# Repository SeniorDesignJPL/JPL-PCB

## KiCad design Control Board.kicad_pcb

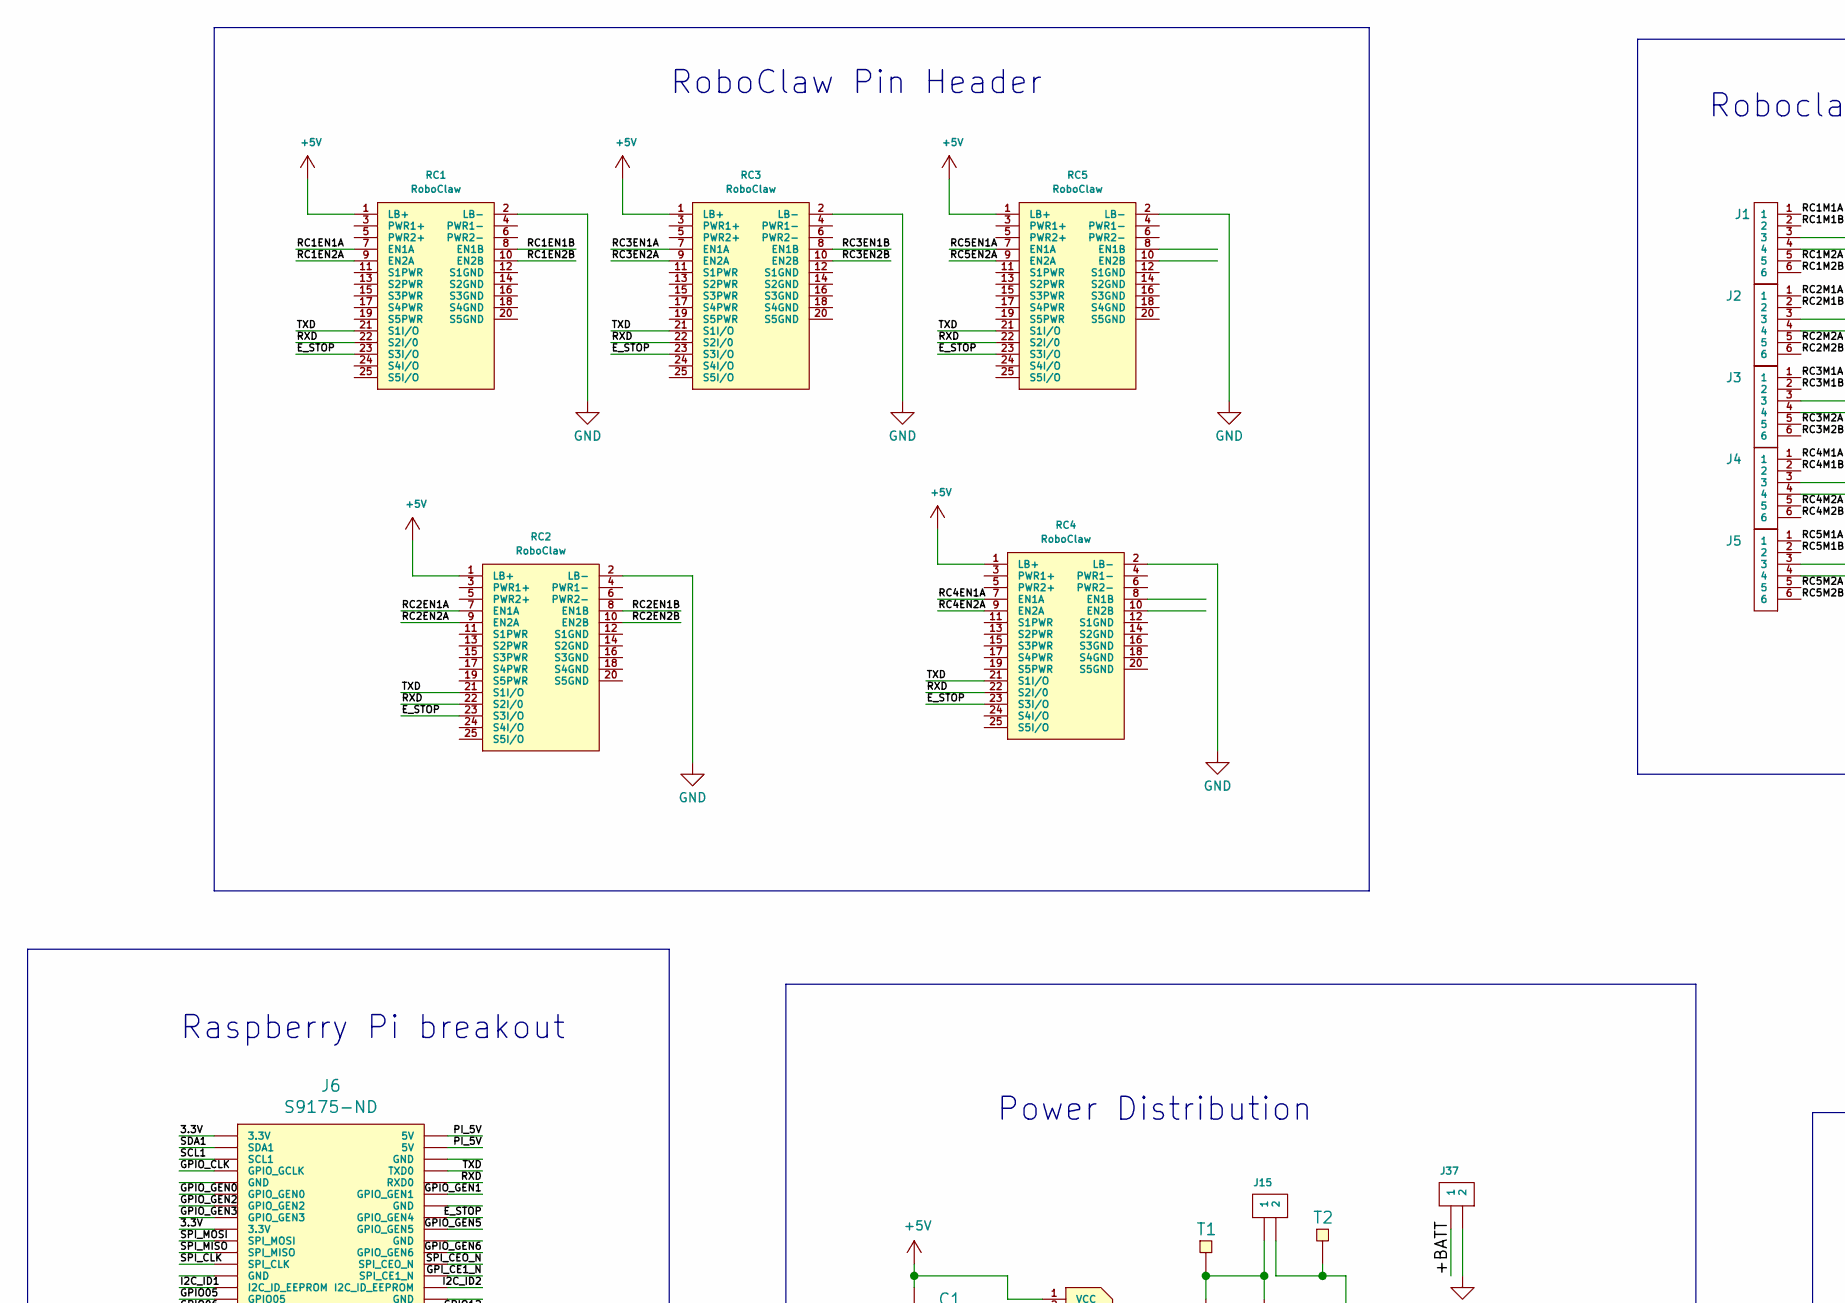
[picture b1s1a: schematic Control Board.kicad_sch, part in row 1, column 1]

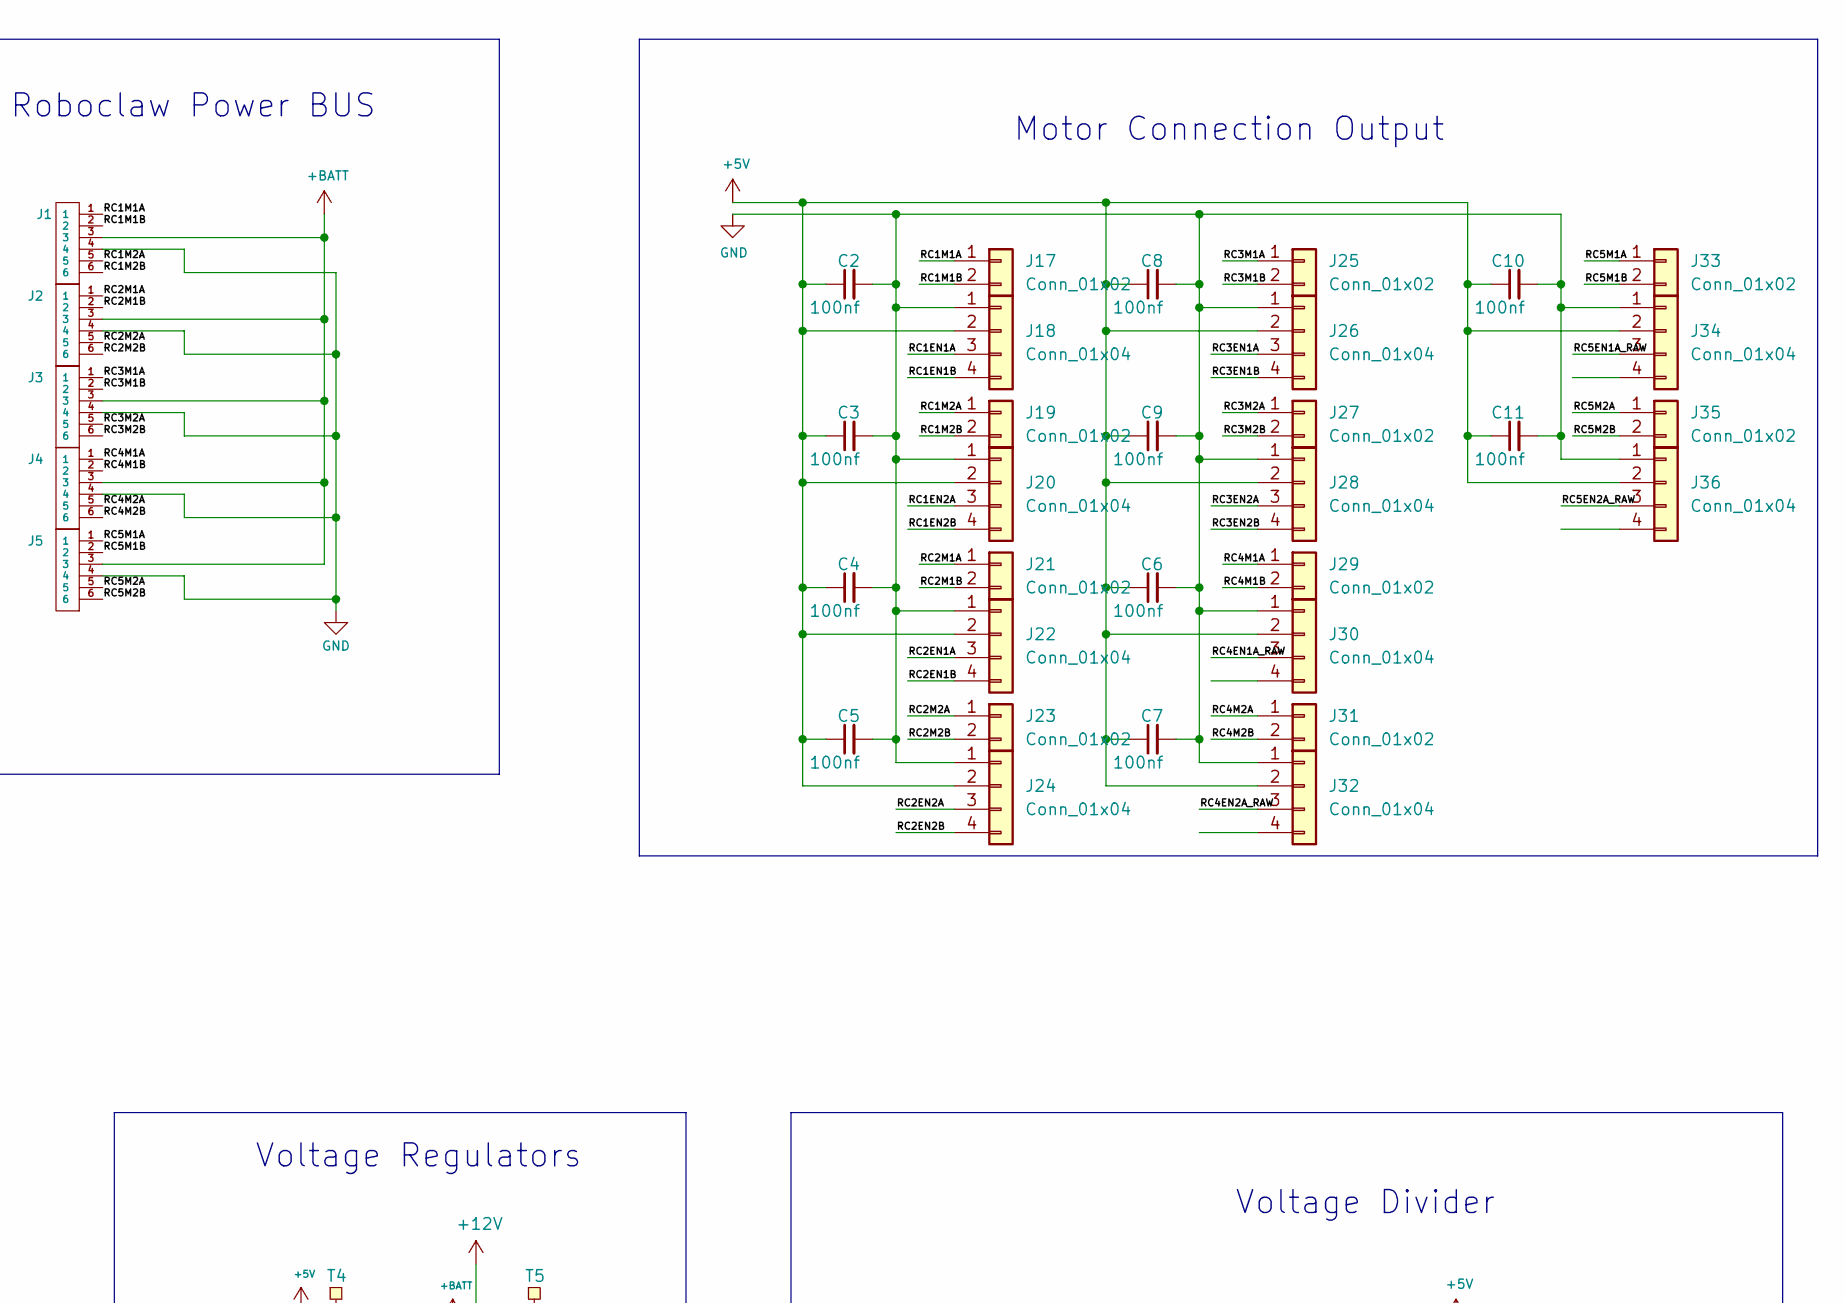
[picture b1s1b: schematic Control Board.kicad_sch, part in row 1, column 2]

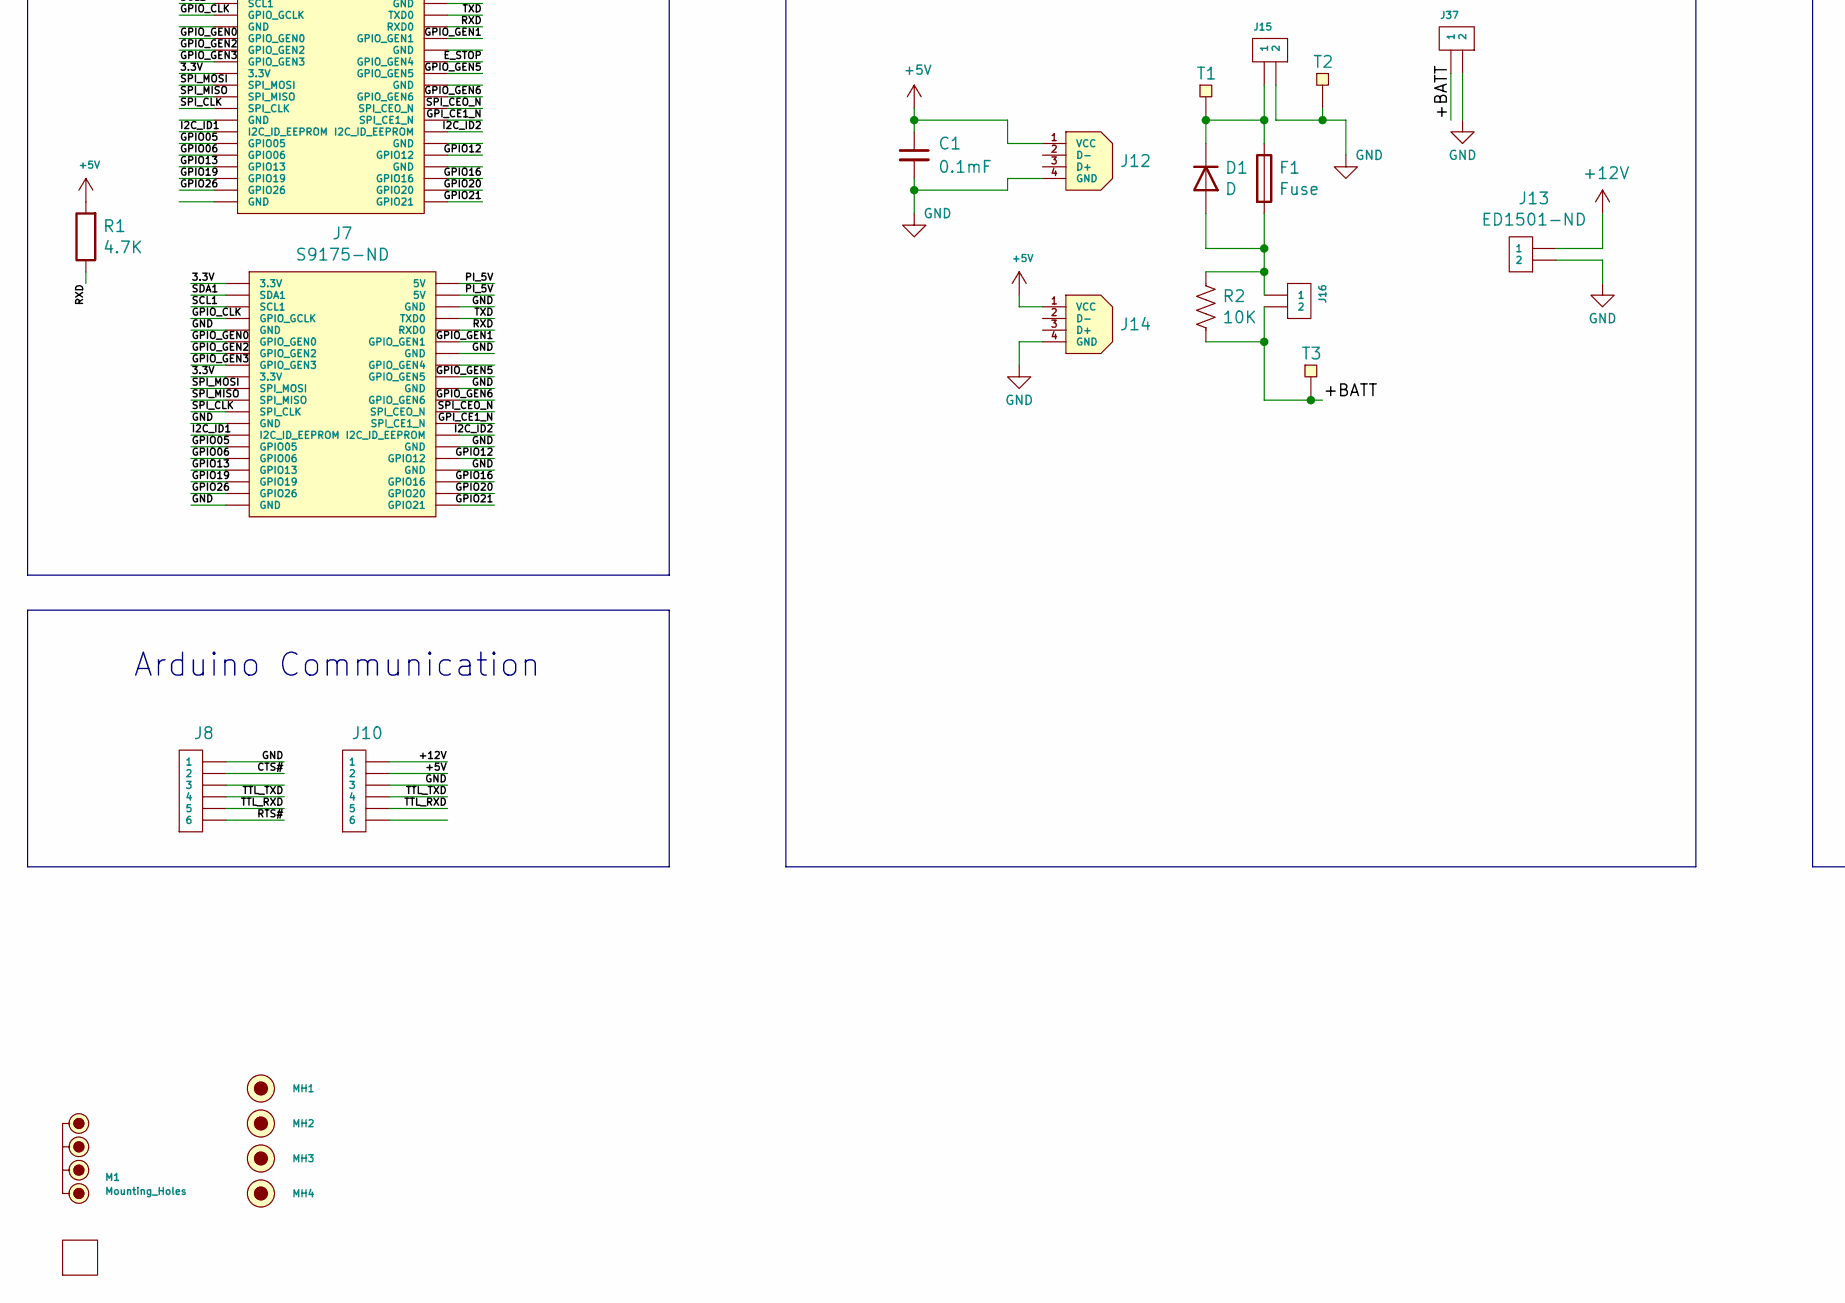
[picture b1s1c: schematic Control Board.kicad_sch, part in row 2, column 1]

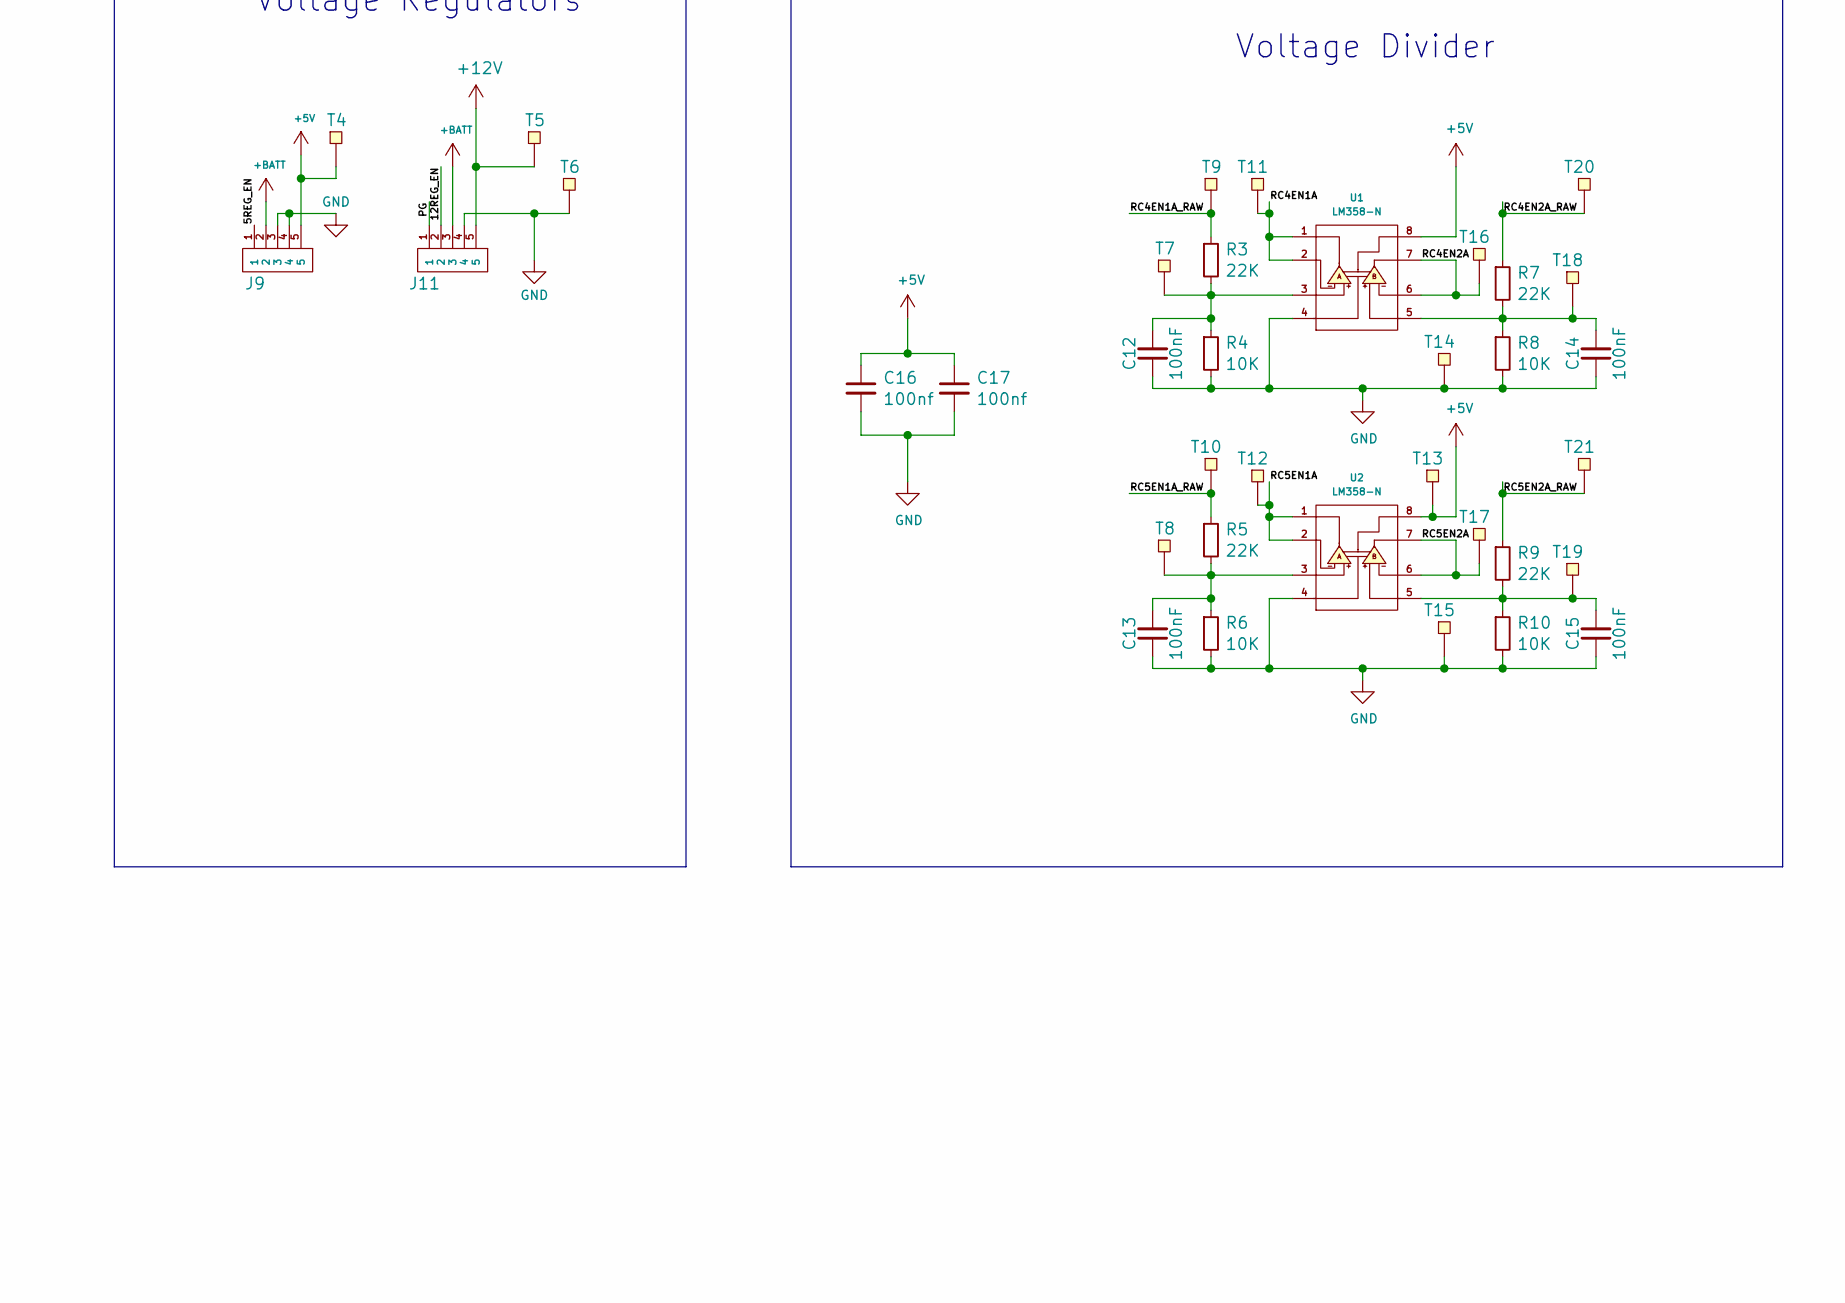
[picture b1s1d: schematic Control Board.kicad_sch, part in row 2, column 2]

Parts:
C1: 0.1mF; R_Axial_DIN0207_L6.3mm_D2.5mm_P7.62mm_Horizontal
C2, C3, C4, C5, C6, C7, C8, C9, C10, C11, C16, C17: 100nf; R_Axial_DIN0207_L6.3mm_D2.5mm_P7.62mm_Horizontal
C12, C13, C14, C15: 100nF; R_Axial_DIN0207_L6.3mm_D2.5mm_P7.62mm_Horizontal
D1: D; 497-2738-5-ND
F1: Fuse; 507-1937-1-ND
J1, J2, J3, J4, J5: ED2627-ND
J6, J7: S9175-ND
J8: 6posheader; 6x1 Header Pin 0.1 Pitch
J9: S7038-ND
J10: 6posheader; 455-1708-ND
J11: S7038-ND; D24V22F12 Regulator
J12, J14: ED2989-ND-USB; ED2989-ND USB Conn
J13: ED1501-ND
J15, J16, J37: ED2580-ND
J17, J19, J21, J23, J25, J27, J29, J31, J33, J35: Conn_01x02; TerminalBlock_Phoenix_PT-1,5-2-3.5-H_1x02_P3.50mm_Horizontal
J18, J20, J22, J24, J26, J28, J30, J32, J34, J36: Conn_01x04; JST_B4B-XH-A(LF)(SN)
M1: Mounting_Holes; Raspberry pi footprint
MH1, MH2, MH3, MH4: #6THRU-HOLE
R1: 4.7K; R_Axial_DIN0207_L6.3mm_D2.5mm_P7.62mm_Horizontal
R2, R4, R6, R8, R10: 10K; R_Axial_DIN0207_L6.3mm_D2.5mm_P7.62mm_Horizontal
R3, R5, R7, R9: 22K; R_Axial_DIN0207_L6.3mm_D2.5mm_P7.62mm_Horizontal
RC1, RC2, RC3, RC4, RC5: RoboClaw; Roboclaw Mount
T1, T2, T3, T4, T5, T6, T7, T8, T9, T10, T11, T12, T13, T14, T15, T16, T17, T18, T19, T20, T21: test_point; TestPoint_Pad_1.0x1.0mm
U1, U2: LM358-N; AE9986-ND
y1: rover_silkscreen; rover_image

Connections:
+5V: C1.1, C2.1, C3.1, C4.1, C5.1, C6.1, C7.1, C8.1, C9.1, C10.1, C11.1, C16.1, C17.1, J9.5, J10.2, J12.1 (VCC), J14.1 (VCC), J18.2, J20.2, J22.2, J24.2, J26.2, J28.2, J30.2, J32.2, J34.2, J36.2, R1.2, RC1.1 (LB+), RC2.1 (LB+), RC3.1 (LB+), RC4.1 (LB+), RC5.1 (LB+), T4.1, T13.1, U1.8 (VCC), U2.8 (VCC)
+12V: J10.1, J11.5, J13.1, T5.1
+BATT: J1.3, J2.3, J3.3, J4.3, J5.3, J9.2, J11.3, J16.2, J37.1, R2.2, T3.1
/3.3V: J6.1 (3.3V), J6.17 (3.3V), J7.1 (3.3V), J7.17 (3.3V)
/5REG_EN: J9.1
/12REG_EN: J11.2
/CTS#: J8.2
/E_STOP: J6.16 (GPIO_GEN4), RC1.23 (S3I/O), RC2.23 (S3I/O), RC3.23 (S3I/O), RC4.23 (S3I/O), RC5.23 (S3I/O)
/GPIO05: J6.29 (GPIO05), J7.29 (GPIO05)
/GPIO06: J6.31 (GPIO06), J7.31 (GPIO06)
/GPIO12: J6.32 (GPIO12), J7.32 (GPIO12)
/GPIO13: J6.33 (GPIO13), J7.33 (GPIO13)
/GPIO16: J6.36 (GPIO16), J7.36 (GPIO16)
/GPIO19: J6.35 (GPIO19), J7.35 (GPIO19)
/GPIO20: J6.38 (GPIO20), J7.38 (GPIO20)
/GPIO21: J6.40 (GPIO21), J7.40 (GPIO21)
/GPIO26: J6.37 (GPIO26), J7.37 (GPIO26)
/GPIO_CLK: J6.7 (GPIO_GCLK), J7.7 (GPIO_GCLK)
/GPIO_GEN0: J6.11 (GPIO_GEN0), J7.11 (GPIO_GEN0)
/GPIO_GEN1: J6.12 (GPIO_GEN1), J7.12 (GPIO_GEN1)
/GPIO_GEN2: J6.13 (GPIO_GEN2), J7.13 (GPIO_GEN2)
/GPIO_GEN3: J6.15 (GPIO_GEN3), J7.15 (GPIO_GEN3)
/GPIO_GEN5: J6.18 (GPIO_GEN5), J7.18 (GPIO_GEN5)
/GPIO_GEN6: J6.22 (GPIO_GEN6), J7.22 (GPIO_GEN6)
/GPI_CE1_N: J6.26 (SPI_CE1_N), J7.26 (SPI_CE1_N)
/I2C_ID1: J6.27 (I2C_ID_EEPROM), J7.27 (I2C_ID_EEPROM)
/I2C_ID2: J6.28 (I2C_ID_EEPROM), J7.28 (I2C_ID_EEPROM)
/PG: J11.1
/PI_5V: J6.2 (5V), J6.4 (5V), J7.2 (5V), J7.4 (5V)
/RC1EN1A: J18.3, RC1.7 (EN1A)
/RC1EN1B: J18.4, RC1.8 (EN1B)
/RC1EN2A: J20.3, RC1.9 (EN2A)
/RC1EN2B: J20.4, RC1.10 (EN2B)
/RC1M1A: J1.1, J17.1
/RC1M1B: J1.2, J17.2
/RC1M2A: J1.5, J19.1
/RC1M2B: J1.6, J19.2
/RC2EN1A: J22.3, RC2.7 (EN1A)
/RC2EN1B: J22.4, RC2.8 (EN1B)
/RC2EN2A: J24.3, RC2.9 (EN2A)
/RC2EN2B: J24.4, RC2.10 (EN2B)
/RC2M1A: J2.1, J21.1
/RC2M1B: J2.2, J21.2
/RC2M2A: J2.5, J23.1
/RC2M2B: J2.6, J23.2
/RC3EN1A: J26.3, RC3.7 (EN1A)
/RC3EN1B: J26.4, RC3.8 (EN1B)
/RC3EN2A: J28.3, RC3.9 (EN2A)
/RC3EN2B: J28.4, RC3.10 (EN2B)
/RC3M1A: J3.1, J25.1
/RC3M1B: J3.2, J25.2
/RC3M2A: J3.5, J27.1
/RC3M2B: J3.6, J27.2
/RC4EN1A: RC4.7 (EN1A), T11.1, U1.1 (OUTA), U1.2 (-INA)
/RC4EN1A_RAW: J30.3, R3.1, T9.1
/RC4EN2A: RC4.9 (EN2A), T16.1, U1.6 (-INB), U1.7 (OUTB)
/RC4EN2A_RAW: J32.3, R7.1, T20.1
/RC4M1A: J4.1, J29.1
/RC4M1B: J4.2, J29.2
/RC4M2A: J4.5, J31.1
/RC4M2B: J4.6, J31.2
/RC5EN1A: RC5.7 (EN1A), T12.1, U2.1 (OUTA), U2.2 (-INA)
/RC5EN1A_RAW: J34.3, R5.1, T10.1
/RC5EN2A: RC5.9 (EN2A), T17.1, U2.6 (-INB), U2.7 (OUTB)
/RC5EN2A_RAW: J36.3, R9.1, T21.1
/RC5M1A: J5.1, J33.1
/RC5M1B: J5.2, J33.2
/RC5M2A: J5.5, J35.1
/RC5M2B: J5.6, J35.2
/RTS#: J8.6
/RXD: J6.10 (RXD0), J7.10 (RXD0), R1.1, RC1.22 (S2I/0), RC2.22 (S2I/0), RC3.22 (S2I/0), RC4.22 (S2I/0), RC5.22 (S2I/0)
/SCL1: J6.5 (SCL1), J7.5 (SCL1)
/SDA1: J6.3 (SDA1), J7.3 (SDA1)
/SPI_CEO_N: J6.24 (SPI_CEO_N), J7.24 (SPI_CEO_N)
/SPI_CLK: J6.23 (SPI_CLK), J7.23 (SPI_CLK)
/SPI_MISO: J6.21 (SPI_MISO), J7.21 (SPI_MISO)
/SPI_MOSI: J6.19 (SPI_MOSI), J7.19 (SPI_MOSI)
/TTL_RXD: J8.5, J10.5
/TTL_TXD: J8.4, J10.4
/TXD: J6.8 (TXD0), J7.8 (TXD0), RC1.21 (S1I/O), RC2.21 (S1I/O), RC3.21 (S1I/O), RC4.21 (S1I/O), RC5.21 (S1I/O)
GND: C1.2, C2.2, C3.2, C4.2, C5.2, C6.2, C7.2, C8.2, C9.2, C10.2, C11.2, C12.1, C13.1, C14.1, C15.1, C16.2, C17.2, J1.4, J2.4, J3.4, J4.4, J5.4, J7.6 (GND), J7.9 (GND), J7.14 (GND), J7.20 (GND), J7.25 (GND), J7.30 (GND), J7.34 (GND), J7.39 (GND), J8.1, J9.3, J9.4, J10.3, J11.4, J12.4 (GND), J13.2, J14.4 (GND), J15.2, J18.1, J20.1, J22.1, J24.1, J26.1, J28.1, J30.1, J32.1, J34.1, J36.1, J37.2, R4.2, R6.2, R8.2, R10.2, RC1.2 (LB-), RC2.2 (LB-), RC3.2 (LB-), RC4.2 (LB-), RC5.2 (LB-), T2.1, T6.1, T14.1, T15.1, U1.4 (GND), U2.4 (GND)
unnamed: C12.2, R3.2, R4.1, T7.1, U1.3 (+INA)
unnamed: C13.2, R5.2, R6.1, T8.1, U2.3 (+INA)
unnamed: C14.2, R7.2, R8.1, T18.1, U1.5 (+INB)
unnamed: C15.2, R9.2, R10.1, T19.1, U2.5 (+INB)
unnamed: D1.1 (K), F1.1, J15.1, T1.1
unnamed: D1.2 (A), F1.2, J16.1, R2.1

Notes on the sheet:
Voltage Regulators
RoboClaw Pin Header
Motor Connection Output
Arduino Communication
Voltage Divider
Raspberry Pi breakout
Power Distribution
Roboclaw Power BUS

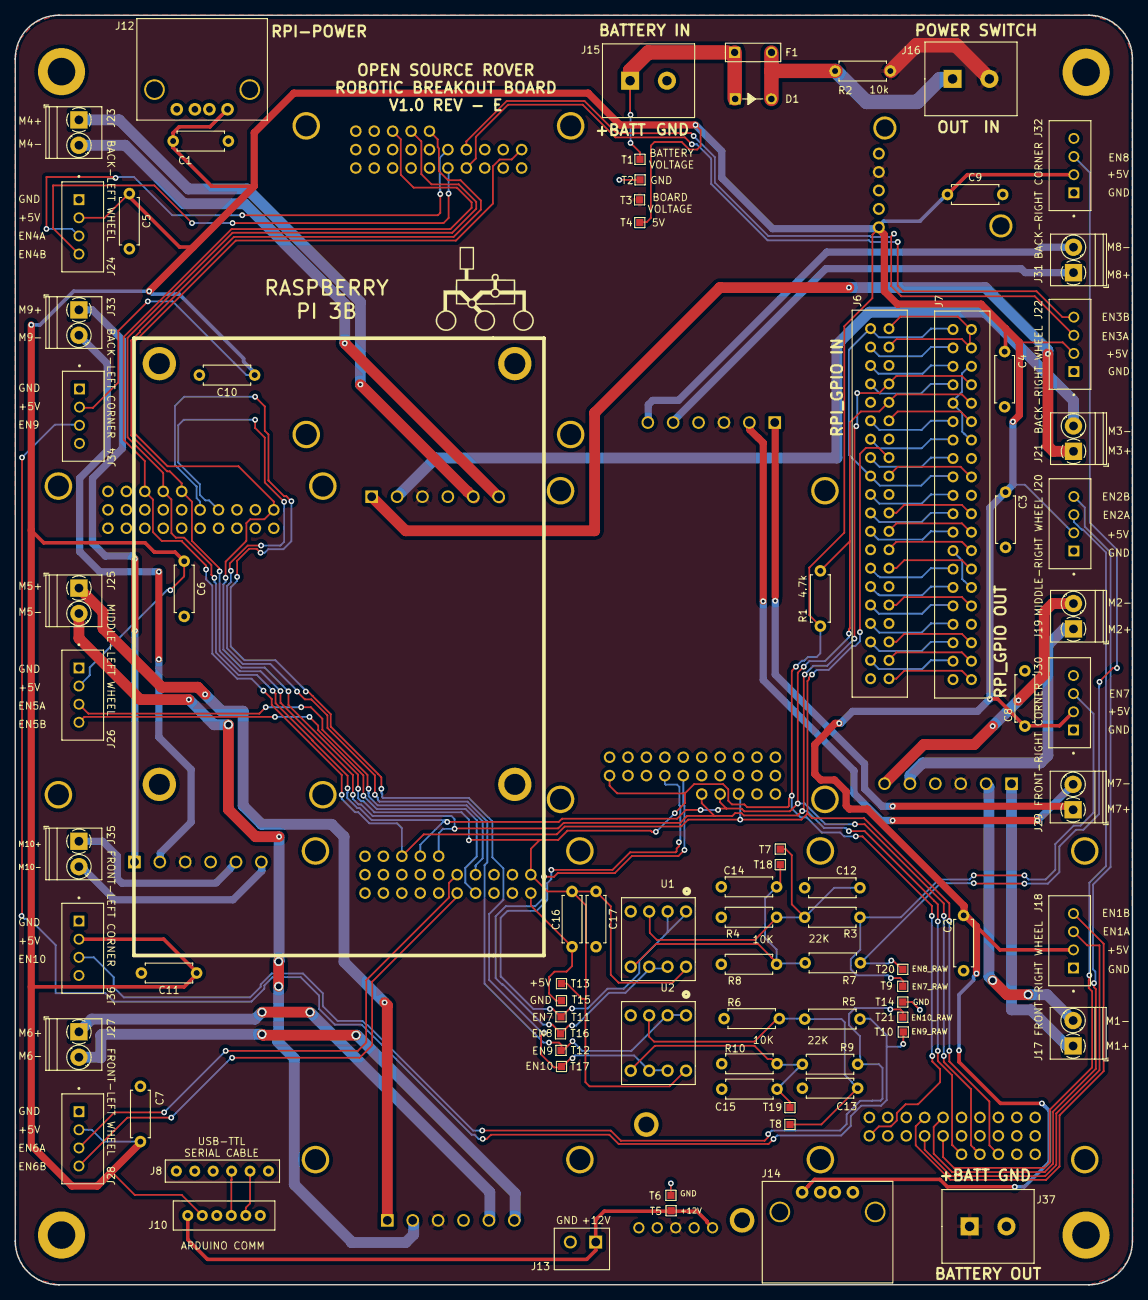
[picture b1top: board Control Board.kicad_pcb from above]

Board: 2 copper layers, 154.0 x 175.0 mm, 100 parts (0 on the bottom side), 82 nets.

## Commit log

2022-12-03 Added JST connectors, screw terminals, and widened traces
2022-12-05 Added gerber files
2022-12-05 new commit
2022-12-05 Removed switch, diode, and fuse from design
